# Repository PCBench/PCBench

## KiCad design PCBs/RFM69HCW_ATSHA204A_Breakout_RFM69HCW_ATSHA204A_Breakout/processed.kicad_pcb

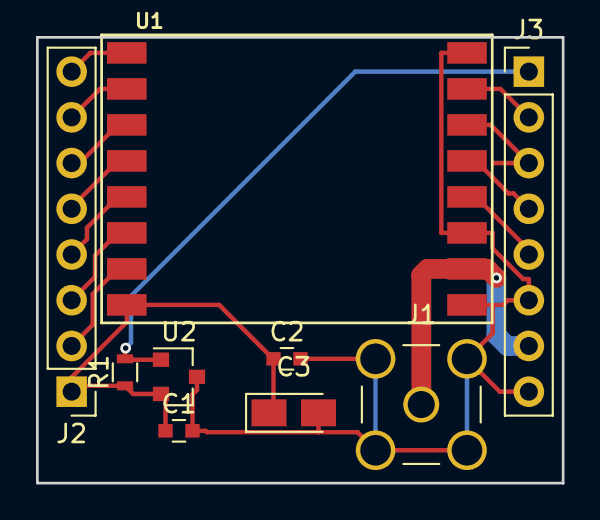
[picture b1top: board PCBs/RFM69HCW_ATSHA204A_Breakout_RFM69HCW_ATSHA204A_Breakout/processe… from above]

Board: 2 copper layers, 29.2 x 24.8 mm, 9 parts (0 on the bottom side), 15 nets.

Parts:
C1, C2: C; C_0603
C3: CP; CP_Tantalum_Case-S_EIA-3216-12_Reflow
J1: CONN_COAXIAL; SMA_THT_Jack_Straight
J2, J3: CONN_01X08; Pin_Header_Straight_1x08_Pitch2.54mm
R1: R; R_0603
U1: RFM69HW; RFM69HW_SMD
U2: ATSHA204A; SOT-23

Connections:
+3V3: C1.1, C2.1, C3.1, J2.1, R1.1, U1.8, U2.2
/ANA: J1.1, J3.7, U1.10
/ATSHA: J3.1, R1.2, U2.1
/DIO0: J2.7, U1.2
/DIO1: J2.6, U1.3
/DIO2: J2.5, U1.4
/DIO3: J2.4, U1.5
/DIO4: J2.3, U1.6
/DIO5: J2.2, U1.7
/MISO: J3.4, U1.13
/MOSI: J3.3, U1.14
/NSS: J3.2, U1.15
/RST: J2.8, U1.1
/SCK: J3.5, U1.12
GND: C1.2, C2.2, C3.2, J1.2, J3.6, J3.8, U1.9, U1.11, U1.16, U2.3

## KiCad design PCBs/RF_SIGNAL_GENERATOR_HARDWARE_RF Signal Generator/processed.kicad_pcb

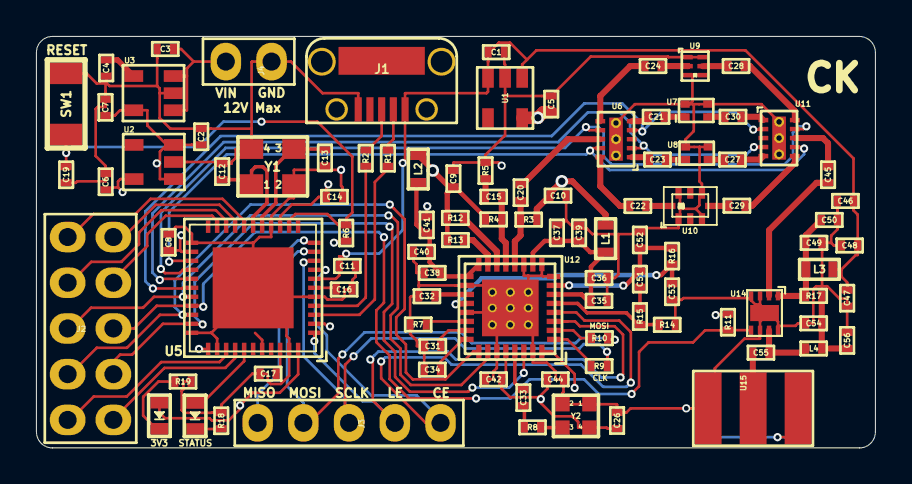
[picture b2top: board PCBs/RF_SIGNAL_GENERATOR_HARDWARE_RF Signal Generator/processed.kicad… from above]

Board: 4 copper layers, 46.6 x 22.9 mm, 98 parts (0 on the bottom side), 80 nets.

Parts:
3V3: Led_Diode; Diode_0603
C1, C2, C3, C4, C5, C6, C7: 2.2uF; SMD_0402
C8, C14, C17, C19, C35, C36, C38, C40, C42, C44, C48, C50, C51: 100nF; SMD_0402
C9, C10, C37, C39, C41: 100pF; SMD_0402
C11, C16, C31, C32, C34: 1uF; SMD_0402
C12, C13: 15pF; SMD_0402
C15, C20, C45, C55: 1nF; SMD_0402
C21, C22, C23, C24, C27, C28, C29, C30, C54: 10pF; SMD_0402
C26, C33, C56: 10nF; SMD_0402
C46, C47: DNP; SMD_0402
C49: 10uF; SMD_0402
C52: 12nF; SMD_0402
C53: 820pF; SMD_0402
J1: USB_MicroB; USB_MicroB_TH
J2: Connector_02x05; PinHeader_2x5_P2.54mm
J3: Connector_01x05; PinHeader_1x5_P2.54mm
J4: Connector_01x02; PinHeader_1x2_P2.54mm
L1, L2, L3: BLM18PG181SN1D; SMD_0603
L4: LQW15AN9N9J80D; SMD_0402
R1, R2: 22; SMD_0402
R3, R4, R5: 49.9; SMD_0402
R6: 10K; SMD_0402
R7: 5.11K; SMD_0402
R8, R9, R10, R12, R13: 0; SMD_0402
R11: 100; SMD_0402
R14: 90.9; SMD_0402
R15: 30.1; SMD_0402
R16: 240; SMD_0402
R17: 1.8; SMD_0402
R18, R19: 1K; SMD_0402
STATUS: Led_Diode; Diode_0603
SW1: RESET_BUTTON; Button_B3U_1000P
U1, U2: LP5907; SOT23_5
U3: MIC5219; SOT23_5
U5: ATMEGA32U4; QFN44_7x7mm_P0.5mm_1EXP_4.5x4.5mm
U6, U11: SKY13322_375LF; MLPD_10
U7: LPF_LP0603A0902ANTR
U8: LPF_LP0603A1842ANTR
U9: LPF_3550LP14A300T
U10: LPF_5515LP15A730E
U12: MAX2871; QFN32_5x5mm_P0.5mm_1EXP_3.1x3.1mm
U14: TRF37A75; WSON8_2x2mm_P0.5mm_1EXP_0.9x1.6mm
U15: SMA_Connector
Y1: 8MHz; Crystal_3.2x2.5mm
Y2: ASTX-13-D-19.200MHz-I05-T; Crystal_2x1.6mm

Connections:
+3V3: 3V3.2, C6.1, C8.1, C14.1, C26.1, C42.2, C44.2, R6.1, R11.1, U2.5, U5.14, U5.24, U5.34, U5.44, U12.28, U12.32, Y2.4
+5V: C1.1, C2.1, C7.1, C11.1, C46.1, C47.1, C48.1, J1.1, L3.1, U1.1, U1.3, U2.1, U2.3, U3.5, U5.2, U5.7
+VBattery: C3.1, J4.2, U3.1, U3.3
/3.3V_RF: C5.1, C9.2, C10.2, L1.1, L2.1, R3.1, R4.1, R12.1, R13.1, U1.5
/D+: R2.2, U5.4
/D-: R1.2, U5.3
/RST: C19.2, R6.2, SW1.1, U5.13
ADC6: J2.10, U5.37
ADC7: J2.9, U5.36
AMP_PWDN: J2.6, R11.2, U5.30, U14.5
GND: C1.2, C2.2, C3.2, C4.2, C5.2, C6.2, C7.2, C8.2, C9.1, C10.1, C11.2, C12.2, C13.2, C14.2, C16.2, C17.2, C19.1, C26.2, C31.1, C32.1, C34.1, C35.1, C36.1, C37.1, C38.1, C39.1, C40.1, C41.1, C42.1, C44.1, C46.2, C47.2, C48.2, C49.2, C50.2, C52.1, C53.1, C54.2, C56.2, J1.5, J4.1, R5.1, R7.2, R14.1, R18.2, R19.2, SW1.2, U1.2, U2.2, U3.2, U5.5, U5.15, U5.23, U5.33, U5.35, U5.43, U5.45, U6.11, U7.3, U7.4, U8.3, U8.4, U9.1, U9.3, U9.4, U9.6, U10.1, U10.3, U10.5, U10.7, U11.11, U12.8, U12.9, U12.11, U12.18, U12.21, U12.27, U12.31, U12.33, U14.3, U14.4, U14.6, U14.8, U14.9, U15.2, U15.3, U15.4, U15.5, Y1.2, Y1.4, Y2.1, Y2.2
MAX2871_CE: J3.1, U5.8, U12.4
MAX2871_LD: J2.7, U5.31, U12.25
MAX2871_LE: J3.2, U5.1, U12.3
MAX2871_MUX: J2.8, U5.32, U12.30
unnamed: C4.1, U3.4
unnamed: C12.1, U5.17, Y1.1
unnamed: C13.1, U5.16, Y1.3
unnamed: C15.2, R5.2
unnamed: C16.1, U5.6
unnamed: C17.1, U5.42
unnamed: C20.2, U6.8
unnamed: C21.1, U7.1
unnamed: C21.2, U6.5
unnamed: C22.1, U10.8
unnamed: C22.2, U6.10
unnamed: C23.1, U8.1
unnamed: C23.2, U6.1
unnamed: C24.1, U9.2
unnamed: C24.2, U6.6
unnamed: C27.1, U11.5
unnamed: C27.2, U8.2
unnamed: C28.1, U11.10
unnamed: C28.2, U9.5
unnamed: C29.1, U11.6
unnamed: C29.2, U10.4
unnamed: C30.1, U11.1
unnamed: C30.2, U7.2
unnamed: C31.2, U12.23
unnamed: C32.2, U12.19
unnamed: C33.1, U12.29
unnamed: C33.2, R8.2
unnamed: C34.2, U12.24
unnamed: C35.2, C36.2, C37.2, C39.2, L1.2, U12.6, U12.10
unnamed: C38.2, C40.2, C41.2, L2.2, U12.16, U12.17
unnamed: C45.1, U14.2
unnamed: C45.2, U11.8
unnamed: C49.1, C50.1, L3.2, R17.1, U14.1
unnamed: C51.1, C52.2, R16.1, U12.7
unnamed: C51.2, R15.1
unnamed: C53.2, R16.2, U12.20
unnamed: C54.1, C56.1, L4.1, R17.2
unnamed: C55.1, L4.2, U14.7
unnamed: C55.2, U15.1
unnamed: R18.1, STATUS.1
unnamed: 3V3.1, R19.1
unnamed: J1.2, R1.1
unnamed: J1.3, R2.1
unnamed: R7.1, U12.22
unnamed: R9.2, U12.1
unnamed: R10.2, U12.2
unnamed: R12.2, U12.14
unnamed: R13.2, U12.15
unnamed: R14.2, R15.2, U12.5
REF_IN: R8.1, Y2.3
RFOUTA_N: C15.1, R4.2, U12.13
RFOUTA_P: C20.1, R3.2, U12.12
RFOUT_EN: J2.5, U5.29, U12.26
RX: J2.3, U5.20
SCL: J2.1, U5.18
SDA: J2.2, U5.19
SPI_CLK: J3.3, R9.1, U5.9
SPI_MISO: J3.5, U5.11
SPI_MOSI: J3.4, R10.1, U5.10
STATUS_LED: STATUS.2, U5.38
SWITCH_V1: U5.25, U6.9, U11.7
SWITCH_V2: U5.26, U6.7, U11.9
SWITCH_V3: U5.27, U6.2, U11.4
SWITCH_V4: U5.28, U6.4, U11.2
TX: J2.4, U5.21

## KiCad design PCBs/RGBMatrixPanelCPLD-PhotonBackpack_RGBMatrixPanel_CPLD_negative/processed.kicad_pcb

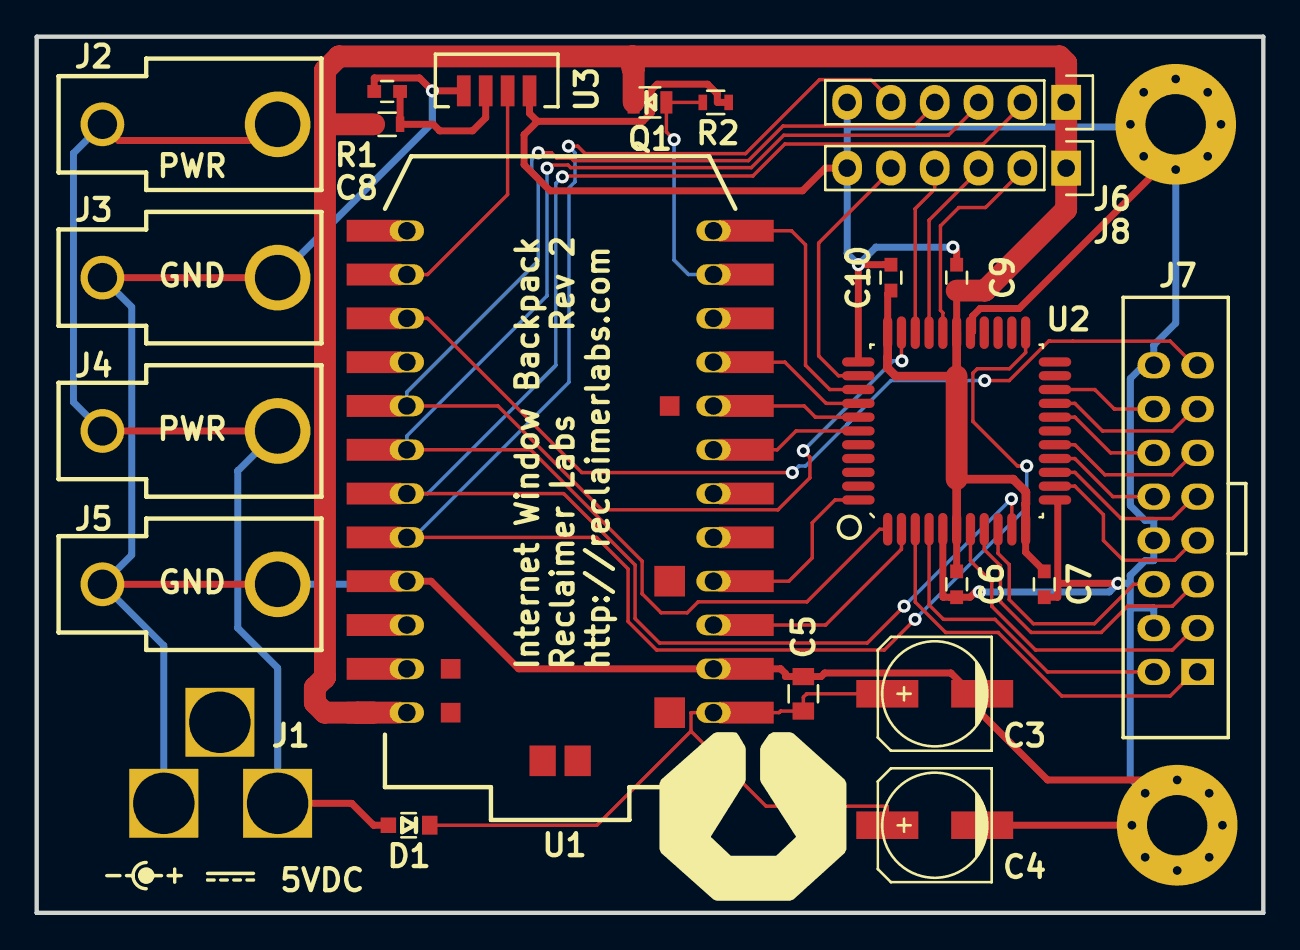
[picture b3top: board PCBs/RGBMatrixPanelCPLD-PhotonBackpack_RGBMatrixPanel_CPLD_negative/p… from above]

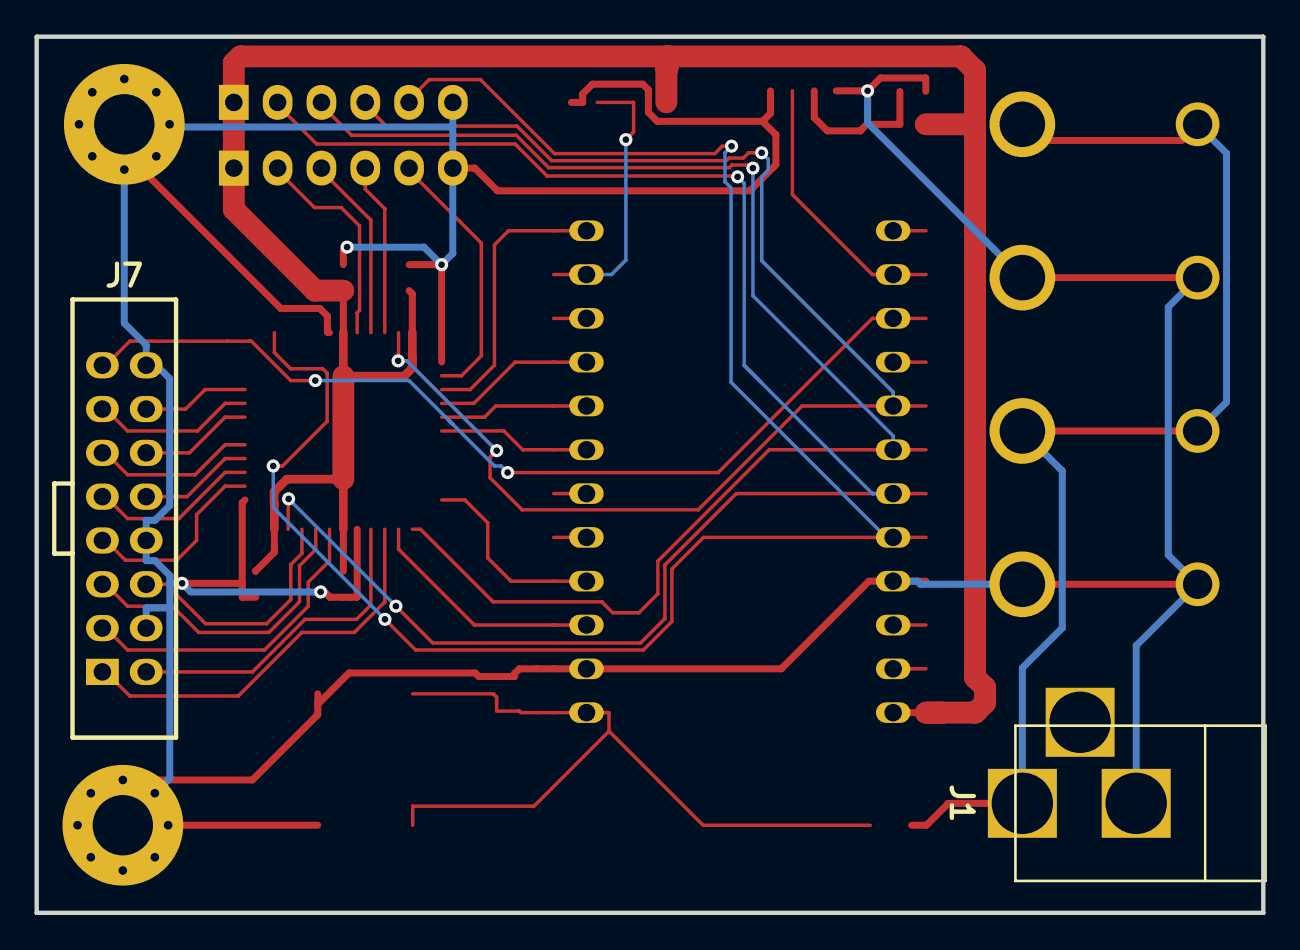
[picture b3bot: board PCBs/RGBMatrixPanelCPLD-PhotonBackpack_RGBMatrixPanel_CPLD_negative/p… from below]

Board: 2 copper layers, 71.1 x 50.8 mm, 25 parts (2 on the bottom side), 34 nets.

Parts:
C3, C4: 100uF; c_elec_6.3x5.7
C5: 10uF; C_0805
C6, C7, C8, C9, C10: 0.1uF; C_0603
D1: D_Schottky; SMini2-F5-B
J1: BARREL_JACK; BARREL_JACK_MPD_EJ508A
J2, J3, J4, J5: CONN_01X01; 3547
J6, J8: CONN_01X06; Socket_Strip_Straight_1x06
J7: CONN_02X08; HEADER_THRU_02x08_POL
Q1: Photo_Trans; Photo_Trans_0805
R1: 100R; R_0603
R2: 10k; R_0603
U1: PHOTON
U2: LC4032V-44TQFP; QFP_44
U3: TSOP75238TT
X3, X4: MTHOLE; MountingHole_3.5mm_Pad_Via

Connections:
+3V3: C6.1, C7.1, C9.1, C10.1, J6.1, J8.1, Q1.C, R1.1, U1.24, U2.6, U2.11, U2.28, U2.33
+5V: D1.2, J1.1, J2.1, J4.1
+5VA: C3.1, C4.1, C5.1, D1.1, U1.1
/A: J7.9, U2.14
/B: J7.10, U2.15
/B1: J7.3, U2.7
/B2: J7.7, U2.13
/C: J7.11, U2.16
/CLK: J7.13, U2.19
/CPLD_B8: J8.2, U2.29
/CPLD_B9: J8.3, U2.30
/CPLD_B10: J8.4, U2.31
/CPLD_B12: J8.5, U2.35
/D: J7.12, U2.18
/G1: J7.2, U2.4
/G2: J7.6, U2.9
/IRDA: U1.14, U3.3
/LAT: J7.14, U2.20
/OE: J7.15, U1.15
/PHOTO: Q1.E, R2.1, U1.11
/R1: J7.1, U2.3
/R2: J7.5, U2.8
/RST_CPLD: U1.12, U2.36
/SPI_MISO: U1.8, U2.38
/SPI_MOSI: U1.7, U2.39
/SPI_SCK: U1.9, U2.37
/TCK: J6.2, U1.19, U2.10
/TDI: J6.3, U1.18, U2.1
/TDO: J6.4, U1.17, U2.32
/TMS: J6.5, U1.20, U2.23
/UART_RX: U1.4, U2.44
/UART_TX: U1.3, U2.2
GND: C3.2, C4.2, C5.2, C6.2, C7.2, C8.2, C9.2, C10.2, J1.2, J3.1, J5.1, J6.6, J7.4, J7.8, J7.16, J8.6, R2.2, U1.2, U1.21, U2.5, U2.12, U2.27, U2.34, U3.1, U3.4, X3.1, X4.1
unnamed: C8.1, R1.2, U3.2

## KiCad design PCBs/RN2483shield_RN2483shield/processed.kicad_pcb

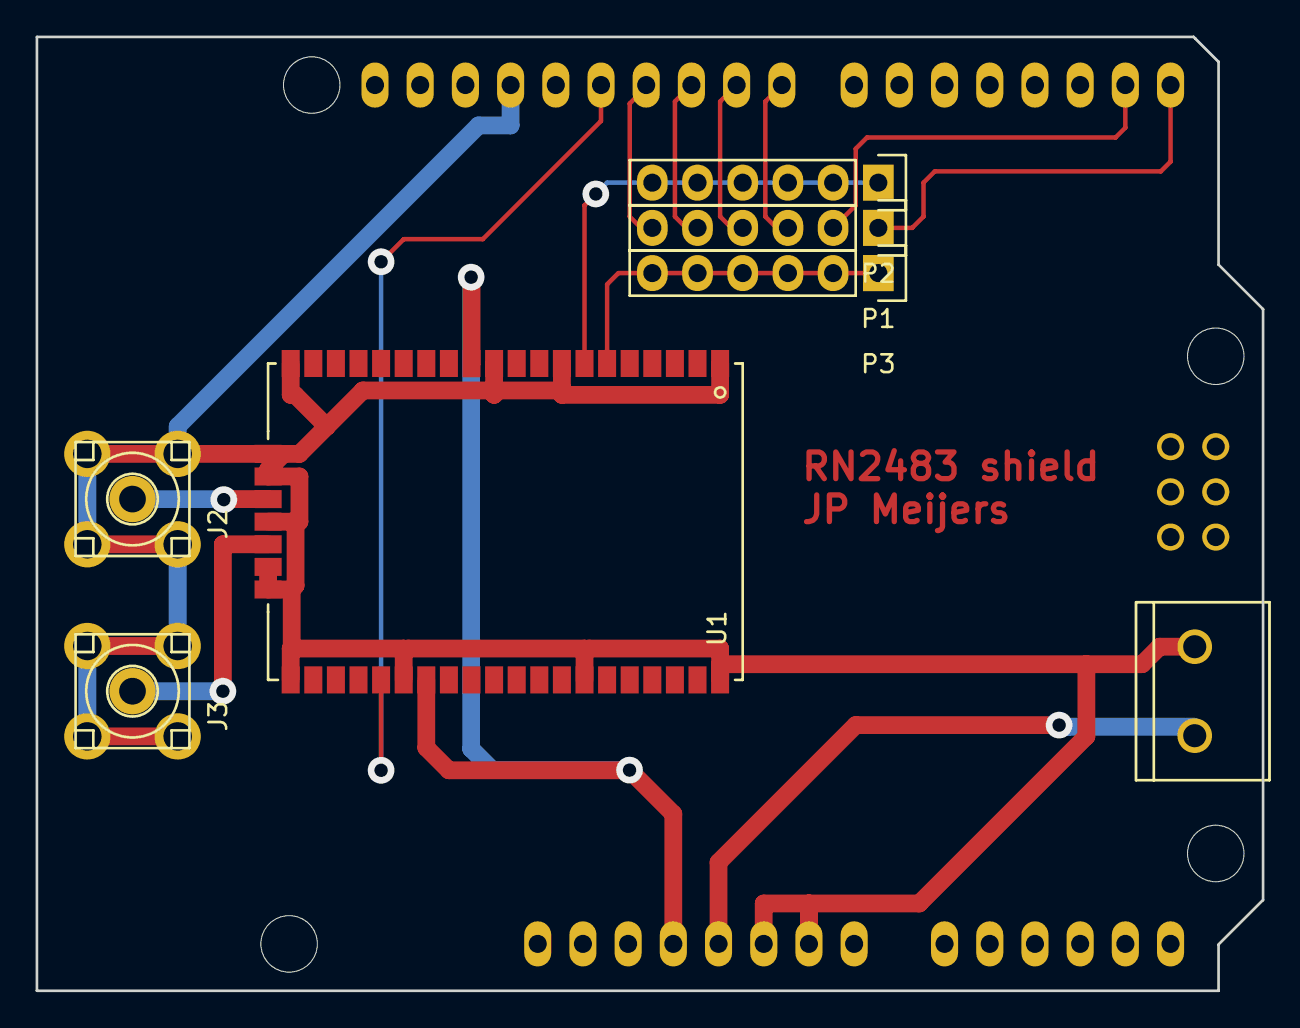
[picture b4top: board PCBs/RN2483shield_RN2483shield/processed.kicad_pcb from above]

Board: 2 copper layers, 68.9 x 53.6 mm, 8 parts (0 on the bottom side), 14 nets.

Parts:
J1: SCREW_TERMINAL; SCREWTERMINAL-5MM-2
J2, J3: SMA; SMA_BOARD_UPRIGHT
P1, P2, P3: CONN_01X06; Socket_Strip_Straight_1x06
SHIELD1: ARDUINO_SHIELD
U1: RN2483

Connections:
3.3VOLT: SHIELD1.3V3, U1.12, U1.34
/AD_P8: P1.3, SHIELD1.8
/AD_P9: P1.4, SHIELD1.9
/AD_P10: P1.5, SHIELD1.10
/AD_P11: P1.6, SHIELD1.11
/HW_RX: P1.1, SHIELD1.0
/HW_TX: P1.2, SHIELD1.1
BATTERY: J1.2, SHIELD1.5V
GND: J1.1, J2.2, J2.3, J2.4, J2.5, J3.2, J3.3, J3.4, J3.5, SHIELD1.GND1, SHIELD1.GND2, SHIELD1.GND3, U1.1, U1.8, U1.11, U1.20, U1.21, U1.22, U1.24, U1.26, U1.27, U1.28, U1.33, U1.41, U1.47
unnamed: J2.1, U1.23
unnamed: J3.1, U1.25
RN_RESET: SHIELD1.12, U1.32
UART_ARDUINO_TO_RADIO: P2.1, P2.2, P2.3, P2.4, P2.5, P2.6, U1.7
UART_RADIO_TO_ARDUINO: P3.1, P3.2, P3.3, P3.4, P3.5, P3.6, U1.6

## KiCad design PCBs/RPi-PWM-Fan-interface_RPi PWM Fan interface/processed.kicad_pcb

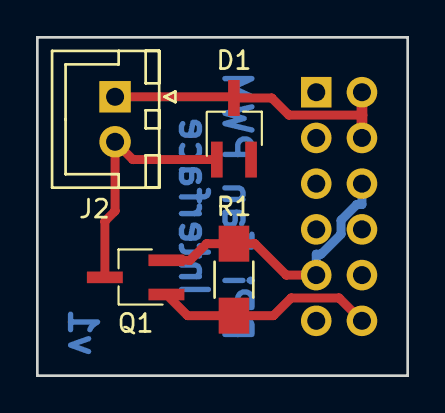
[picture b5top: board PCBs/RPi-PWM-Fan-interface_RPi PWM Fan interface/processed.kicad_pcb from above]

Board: 2 copper layers, 20.6 x 18.8 mm, 5 parts (0 on the bottom side), 4 nets.

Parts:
D1: Schottky; TSOT-23_HandSoldering
J1: CONN_02X06; Socket_Strip_Straight_2x06_Pitch2.54mm
J2: JST_XH_01X02; JST_XH_B02B-XH-A_02x2.50mm_Straight
Q1: MOSFET; TSOT-23_HandSoldering
R1: 100K; R_1206_HandSoldering

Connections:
+5V: D1.3, J1.2, J1.4, J2.1
GND: J1.6, J1.9, Q1.2, R1.2
unnamed: D1.1, J2.2, Q1.3
unnamed: J1.12, Q1.1, R1.1

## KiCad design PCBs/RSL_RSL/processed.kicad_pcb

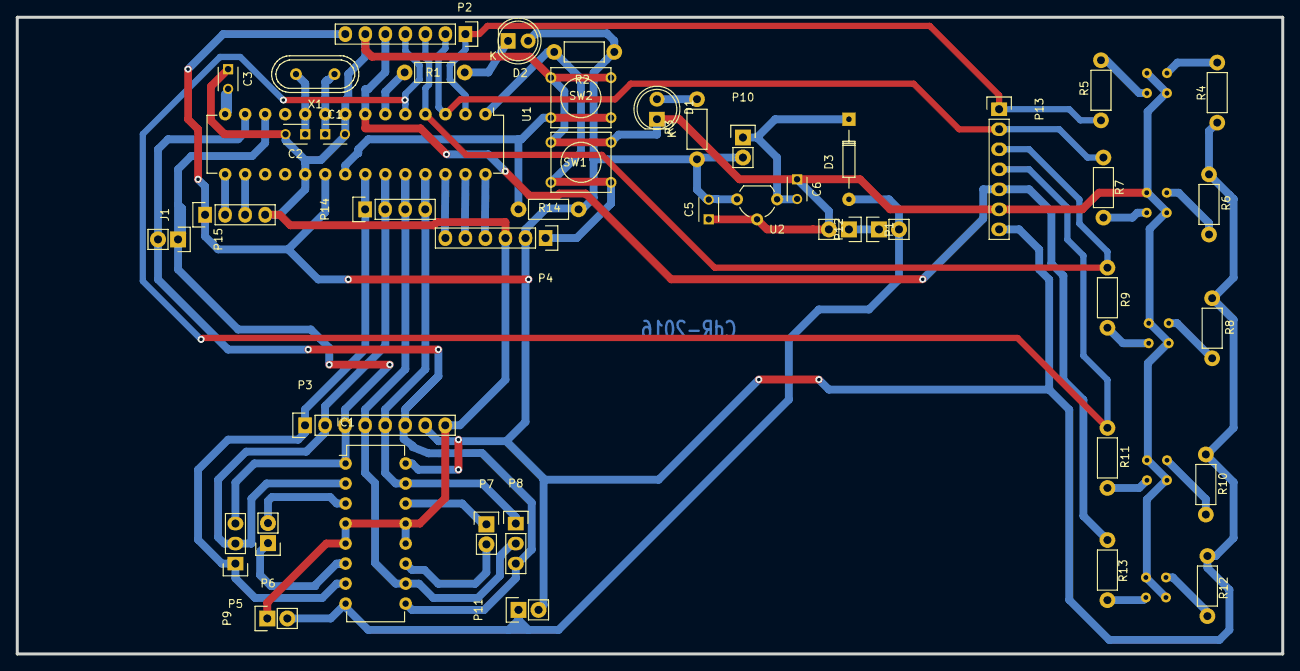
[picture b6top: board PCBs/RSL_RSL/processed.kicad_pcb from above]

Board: 2 copper layers, 160.5 x 80.8 mm, 49 parts (0 on the bottom side), 43 nets.

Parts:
C1: C-crsital; C_Disc_D3_P2.5
C2: C-cristal; C_Disc_D3_P2.5
C3: C; C_Disc_D3_P2.5
C5, C6: C-reg; C_Disc_D3_P2.5
D1: PWR; LED-5MM
D2: RUN; LED-5MM
D3: D_Small; Diode_DO-35_SOD27_Horizontal_RM10
IC1: L293D; DIP-16_W7.62mm
J1: USB; Pin_Header_Straight_1x04
P1: Alimentacion; Pin_Header_Straight_1x02
P2, P13: Pines_Sensores; Socket_Strip_Straight_1x07
P3: Pines_ Driver_M; Socket_Strip_Straight_1x08
P4: pickit; Socket_Strip_Straight_1x06
P5: 2A-1A-1.2E; Pin_Header_Straight_1x03
P6: motor1; Pin_Header_Straight_1x02
P7: motor2; Pin_Header_Straight_1x02
P8: E3.4-3A-4A; Pin_Header_Straight_1x03
P9: alimtacionMOTORES; Pin_Header_Straight_1x02
P10: BAT; Pin_Header_Straight_1x02
P11: jp1; Pin_Header_Straight_1x02
P12: PWRSW; Pin_Header_Straight_1x02
P14: Ctrl_Dir; Pin_Header_Straight_1x04
P15: PWM; Pin_Header_Straight_1x02
R1: 470; Resistor_Horizontal_RM7mm
R2: 10K; Resistor_Horizontal_RM7mm
R3, R4, R5, R6, R7, R8, R9, R10, R11, R12, R13, R14: R; Resistor_Horizontal_RM7mm
SW1: reset; SW_PUSH_SMALL
SW2: int0; SW_PUSH_SMALL
U1: PIC18F2550; DIP-28_W7.62mm
U2: 7805; TO-92_Molded_Wide
U3, U4, U5, U6, U7: CNY70; cny70-4
X1: CRYSTAL; Crystal_HC49-U_Vertical

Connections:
/0: R14.2, SW2.1, U1.21
/5: P4.6, U1.26
/6: P4.5, U1.27
/7: P4.4, U1.28
/D+: J1.3, U1.16
/D-: J1.2, U1.15
/driver_motores/1A: IC1.2, P3.2, P5.2, P14.2, U1.23
/driver_motores/2A: IC1.7, P3.1, P5.1, P14.1, U1.22
/driver_motores/3A: IC1.10, P3.4, P8.2, P14.3, U1.24
/driver_motores/4A: IC1.15, P3.5, P8.1, P14.4, U1.25
/driver_motores/E-1.2: IC1.1, P3.3, P5.3, P15.1, U1.12
/driver_motores/E-3.4: IC1.9, P3.6, P8.3, P15.2, U1.13
/r: P4.1, R2.2, SW1.2, U1.1
/run: R1.2, U1.6
/sensores/sens0: P2.1, P13.1, R5.1, U1.2
/sensores/sens1: P2.2, P13.2, R7.1, U1.3
/sensores/sens2: P2.3, P13.3, R9.1, U1.4
/sensores/sens3: P2.4, P13.4, R11.1, U1.5
/sensores/sens4: P2.5, P13.5, R13.1, U1.7
GND: C1.2, C2.2, C3.1, C5.1, C6.1, D1.1, IC1.4, IC1.5, IC1.12, IC1.13, J1.4, P1.2, P2.6, P3.8, P4.3, P9.1, P13.6, SW1.1, SW2.2, U1.8, U1.19, U2.2, U3.E, U3.K, U4.E, U4.K, U5.E, U5.K, U6.E, U6.K, U7.E, U7.K
unnamed: C1.1, U1.9, X1.1
unnamed: C2.1, U1.10, X1.2
unnamed: C3.2, U1.14
unnamed: C6.2, D3.1, P10.1, U2.1
unnamed: D1.2, R3.2
unnamed: D2.1, R1.1
unnamed: IC1.3, P6.2
unnamed: IC1.6, P6.1
unnamed: IC1.11, P7.2
unnamed: IC1.14, P7.1
unnamed: P1.1, P12.1
unnamed: R4.2, U3.A
unnamed: R5.2, U3.C
unnamed: R6.2, U4.A
unnamed: R7.2, U4.C
unnamed: R8.2, U5.A
unnamed: R9.2, U5.C
unnamed: R10.2, U6.A
unnamed: R11.2, U6.C
unnamed: R12.2, U7.A
unnamed: R13.2, U7.C
VCC: C5.2, D2.2, IC1.16, J1.1, P2.7, P3.7, P4.2, P10.2, P11.2, P13.7, R2.1, R3.1, R4.1, R6.1, R8.1, R10.1, R12.1, R14.1, U1.20, U2.3
VCC2: D3.2, IC1.8, P9.2, P11.1, P12.2

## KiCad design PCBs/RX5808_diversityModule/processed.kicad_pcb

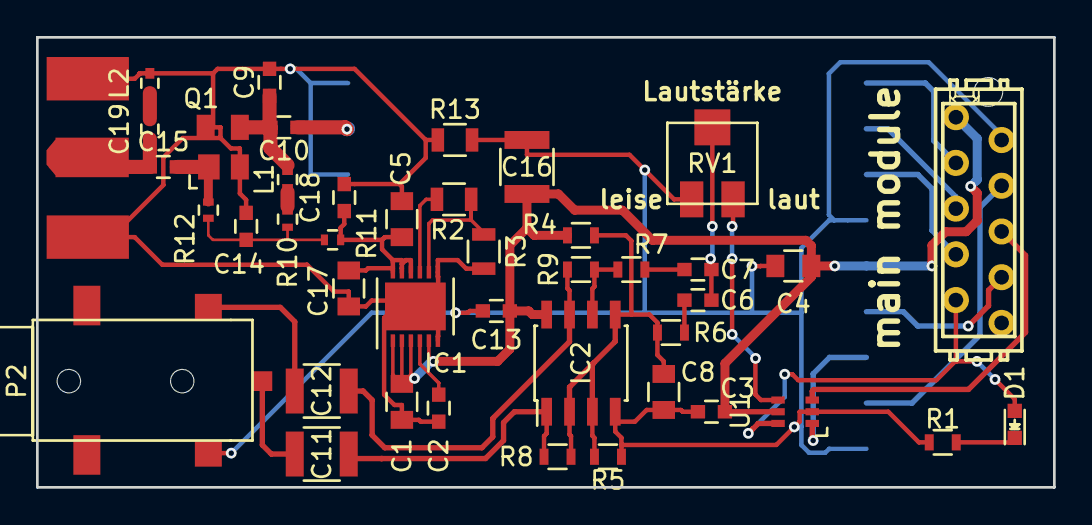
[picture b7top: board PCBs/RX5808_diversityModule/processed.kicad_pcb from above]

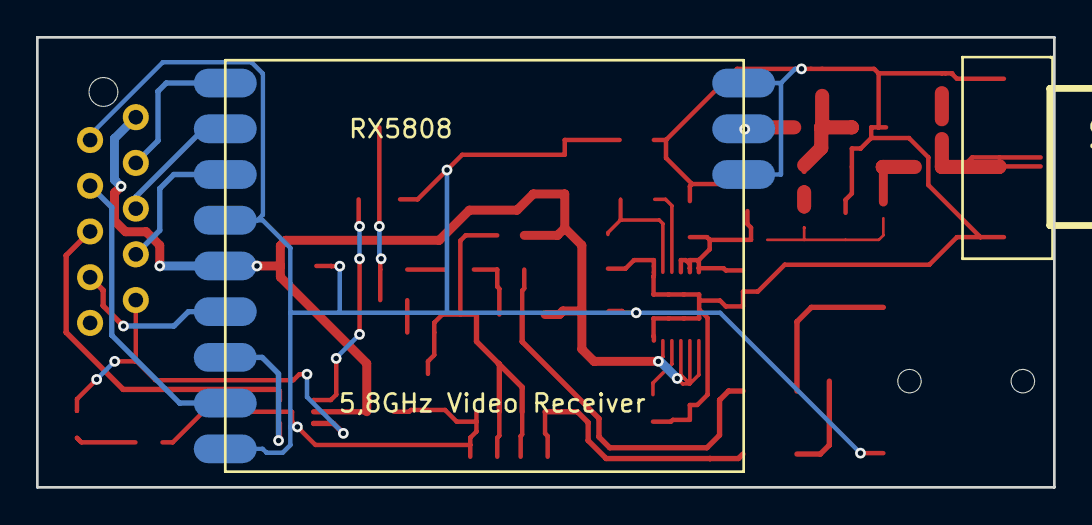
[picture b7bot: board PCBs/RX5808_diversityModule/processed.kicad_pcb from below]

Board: 2 copper layers, 56.5 x 25.0 mm, 44 parts (2 on the bottom side), 33 nets.

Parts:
C1, C4, C5, C17: 10u; C_0805
C2: 10n; C_0603
C3, C13, C18: 100n; C_0603
C6, C7: 1u; C_0603
C8: 22u; C_0805
C9, C10: 1p; C_0603
C11, C12, C16: 100µ; C_1210
C14: 33pF; C_0603
C15: 22p; C_0603
C19: 2,2pF; C_0402
D1: red; LED_0603
IC1: LP38798; DFN-12-1EP_4x4mm_Pitch0.5mm
IC2: TDA1308A; SOIC-8_3.9x4.9mm_Pitch1.27mm
L1: 1,8nH; R_0402
L2: 1,8nH; C_0402
P1: CONN_02X05; MICROMATCH-10
P2: CONN_01X03; LUM1503-03
Q1: BFP840; SOT-143
R1: 220; R_0603
R2: 21k 0,1%; R_0805
R3: 14k 0,1%; R_0805
R4, R5: 10k; R_0603
R6, R7: 3,9k; R_0603
R8, R9: 39k; R_0603
R10, R11: 51; R_0402
R12: 27k; R_0402
R13: 0; R_0805
RV1: POT; Poti-SMD-Model-23A
SMA_E1: SMA_EDGE; SMA_EDGE_Johnson_142-0701-801
U1: sn74lvc1g3157; SC-70-6
U2: RX5808

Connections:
+5V: C1.1, C3.1, C4.1, C13.1, C16.1, IC1.1, IC1.2, IC1.3, IC1.5, IC2.8, P1.1, R4.1, U1.5, U2.8
/+3,0V: C5.1, C17.1, C18.1, IC1.10, IC1.11, IC1.12, R11.2
/audio1: P1.6, U1.3
/clk: P1.7, U2.6
/data: P1.3, U2.4
/rssi: P1.8, U2.9
/ss: P1.5, U2.5
/switch: D1.2, P1.9, U1.6
/video2: P1.4, U2.11
GND: C3.2, C4.2, C8.2, C13.2, C16.2, IC2.4, P1.2, P2.1, R1.2, R5.2, R13.1, RV1.3, U1.2, U2.7, U2.12
GNDA: C1.2, C2.2, C5.2, C9.2, C14.1, C17.2, C18.2, IC1.6, IC1.7, IC1.13, L2.2, Q1.2, Q1.4, R3.2, R13.2, SMA_E1.0, SMA_E1.2, U2.1, U2.3
unnamed: C2.1, IC1.4
unnamed: C6.1, R6.2
unnamed: C6.2, C7.2, RV1.2
unnamed: C7.1, R7.2
unnamed: C8.1, IC2.2, IC2.3, IC2.5, R4.2, R5.1, R6.1, R8.2
unnamed: C9.1, C10.1, L1.2, Q1.3
unnamed: C10.2, U2.2
unnamed: C11.1, IC2.1, R8.1
unnamed: C11.2, P2.2
unnamed: C12.1, IC2.7, R9.1
unnamed: C12.2, P2.3
unnamed: C14.2, R10.1, R11.1, R12.2
unnamed: C15.1, C19.1, SMA_E1.1
unnamed: C15.2, Q1.1, R12.1
unnamed: C19.2, L2.1
unnamed: D1.1, R1.1
unnamed: IC1.8, R2.2, R3.1
unnamed: IC1.9, R2.1
unnamed: IC2.6, R7.1, R9.2
unnamed: L1.1, R10.2
unnamed: RV1.1, U1.4
unnamed: U1.1, U2.10
